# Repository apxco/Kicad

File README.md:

Ein Paar Projekte von mir zur Dokumentation und  vlt. ist es jemandem nützlich. 

Würde mich freuen jedenfalls.

Benutzung auf eigene Gefahr!

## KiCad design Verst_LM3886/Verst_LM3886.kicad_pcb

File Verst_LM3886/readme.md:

Verstärkermodul mit LM3886<br/>
<br/>
Für meine Bastelecke brauche ich einen Verstärker. Der sollte nicht hörbar rauschen oder brummen.  Was das vorhandene Modul auf Basis LM3886 leider tut. Zumindest bei niedrieger einstellung des Lautstärkepotis, warum auch immer. Ich bekomme es nicht abgestellt und da ich sowieso mehr Kanäle brauche, dieses Projekt.<br/>
<br/>
Ziele:<br/>
kein hörbares Rauschen oder Brummen.<br/>
Leistung, ich habe einen 16v Traffo und der Kühlkörper ist vorhanden, das muss genügen.
<br/>

04.01.2026  Erster Entwurf Schaltplan und Platine. 
07.02.2026  Erster Platinenentwurf fertiggestellt.
<br/>

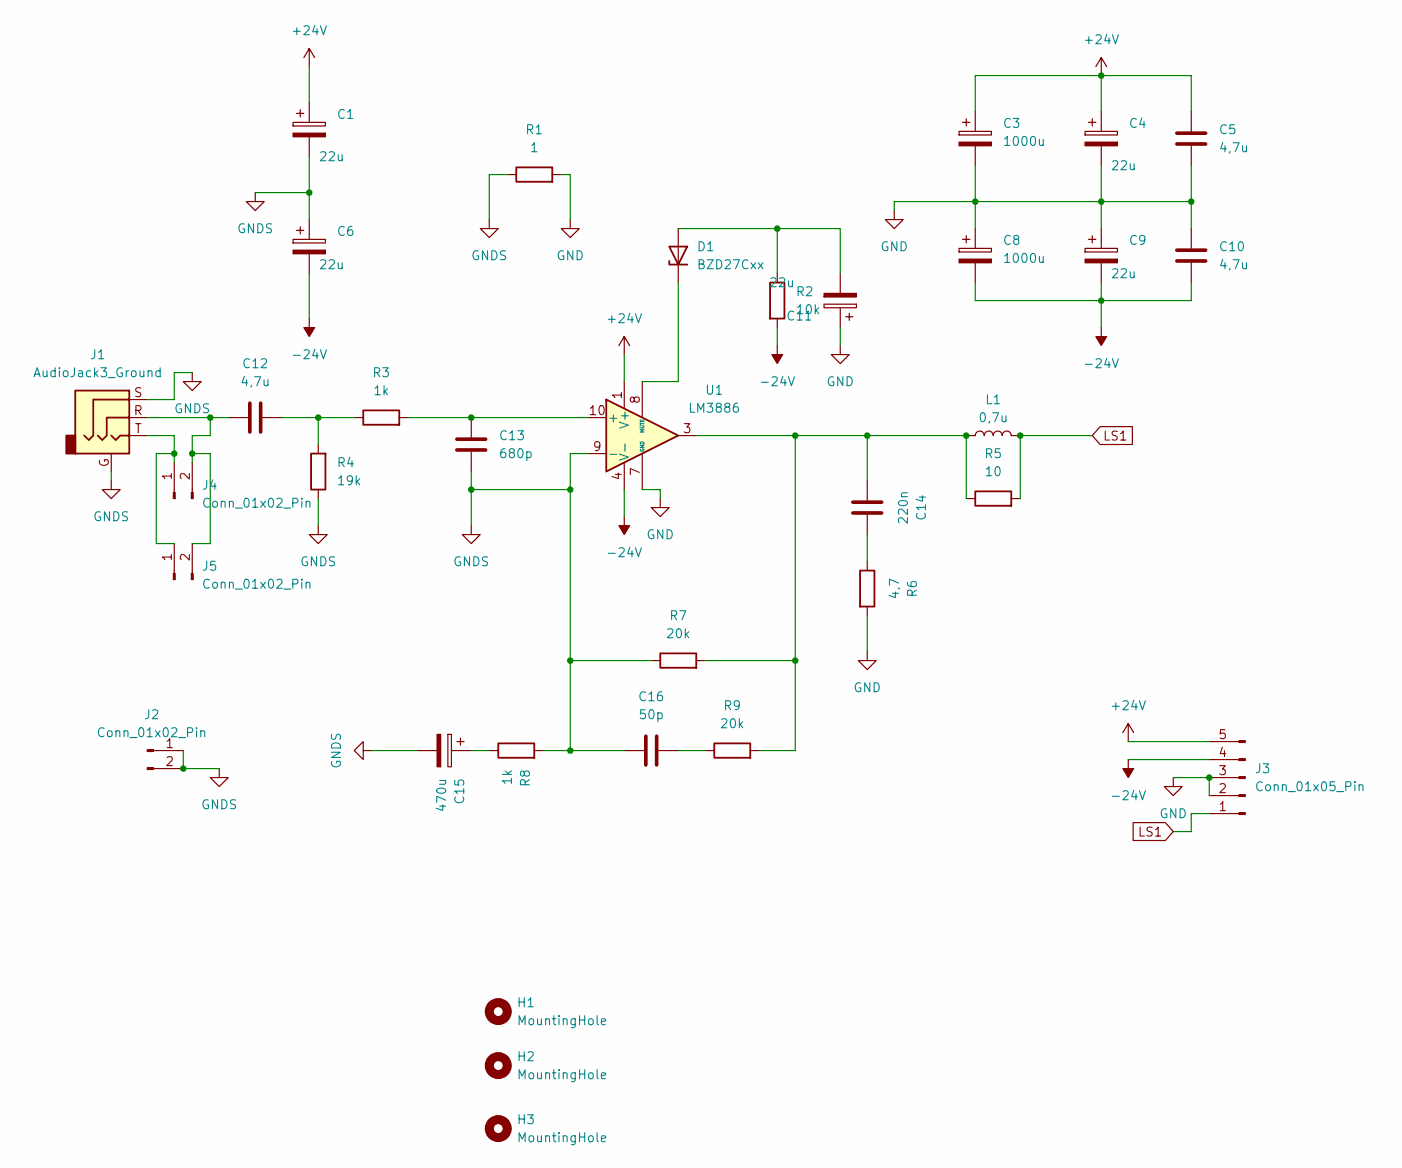
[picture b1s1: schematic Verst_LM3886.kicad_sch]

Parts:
C1, C4, C6, C9, C11: 22u; CP_Radial_D6.3mm_P2.50mm
C3, C8: 1000u; CP_Radial_D10.0mm_P5.00mm_P7.50mm
C5, C10: 4,7u; C_1210_3225Metric_Pad1.33x2.70mm_HandSolder
C12: 4,7u; C_Disc_D8.0mm_W5.0mm_P7.50mm
C13: 680p; C_Rect_L7.0mm_W3.5mm_P2.50mm_P5.00mm
C14: 220n; C_Rect_L7.0mm_W3.5mm_P2.50mm_P5.00mm
C15: 470u; C_Radial_D10.0mm_H20.0mm_P5.00mm
C16: 50p; C_0805_2012Metric_Pad1.18x1.45mm_HandSolder
D1: BZD27Cxx; D_SMF
H1, H2, H3: MountingHole; MountingHole_3.2mm_M3
J1: AudioJack3_Ground; Jack_3.5mm_PJ320E_Horizontal
J2: Conn_01x02_Pin; JST_NV_B02P-NV_1x02_P5.00mm_Vertical
J3: Conn_01x05_Pin; PhoenixContact_MSTBVA_2,5_5-G_1x05_P5.00mm_Vertical
J4, J5: Conn_01x02_Pin; PinHeader_1x02_P1.27mm_Vertical
L1: 0,7u; L_Radial_L9.1mm_W9.1mm_Px6.35mm_Py6.35mm_Pulse_LP-25
R1: 1; R_Axial_DIN0204_L3.6mm_D1.6mm_P2.54mm_Vertical
R2: 10k; R_0805_2012Metric_Pad1.20x1.40mm_HandSolder
R3, R8: 1k; R_0805_2012Metric_Pad1.20x1.40mm_HandSolder
R4: 19k; R_0805_2012Metric_Pad1.20x1.40mm_HandSolder
R5: 10; R_Axial_DIN0309_L9.0mm_D3.2mm_P12.70mm_Horizontal
R6: 4,7; R_Axial_DIN0309_L9.0mm_D3.2mm_P12.70mm_Horizontal
R7, R9: 20k; R_0805_2012Metric_Pad1.20x1.40mm_HandSolder
U1: LM3886; TO-220-11_P3.4x5.08mm_StaggerOdd_Lead4.58mm_Vertical

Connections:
+24V: C1.1, C3.1, C4.1, C5.1, J3.5, U1.1 (V+), U1.5 (V+)
-24V: C6.2, C8.2, C9.2, C10.2, J3.4, R2.2, U1.4 (V-)
GND: C3.2, C4.2, C5.2, C8.1, C9.1, C10.1, C11.1, J3.2, J3.3, R1.2, R6.2, U1.7 (GND)
GNDS: C1.2, C6.1, C13.1, C15.2, C16.1, J1.G, J1.S, J2.1, J2.2, R1.1, R4.1, R7.1, R8.2, U1.9 (-)
LS1: J3.1, L1.2, R5.2
unnamed: C12.1, R3.1, R4.2
unnamed: C14.1, L1.1, R5.1, R7.2, R9.2, U1.3
unnamed: C14.2, R6.1
unnamed: C15.1, R8.1
unnamed: C16.2, R9.1
unnamed: C11.2, D1.2 (A), R2.1
unnamed: D1.1 (K), U1.8 (MUTE)
unnamed: J1.T, J4.1, J5.1
unnamed: C12.2, J1.R, J4.2, J5.2
unnamed: C13.2, R3.2, U1.10 (+)

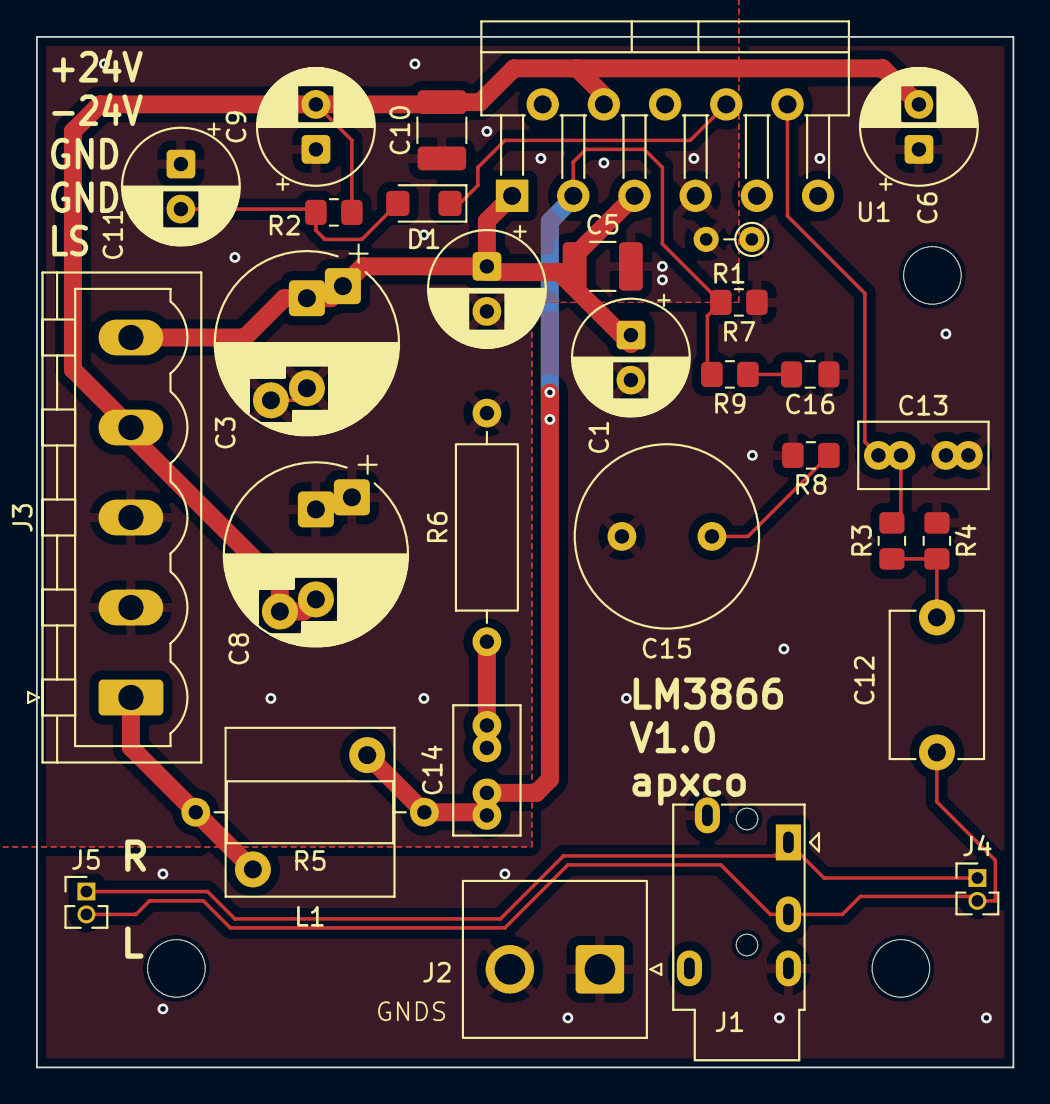
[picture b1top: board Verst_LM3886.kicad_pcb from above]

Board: 2 copper layers, 54.2 x 57.2 mm, 34 parts (0 on the bottom side), 15 nets.

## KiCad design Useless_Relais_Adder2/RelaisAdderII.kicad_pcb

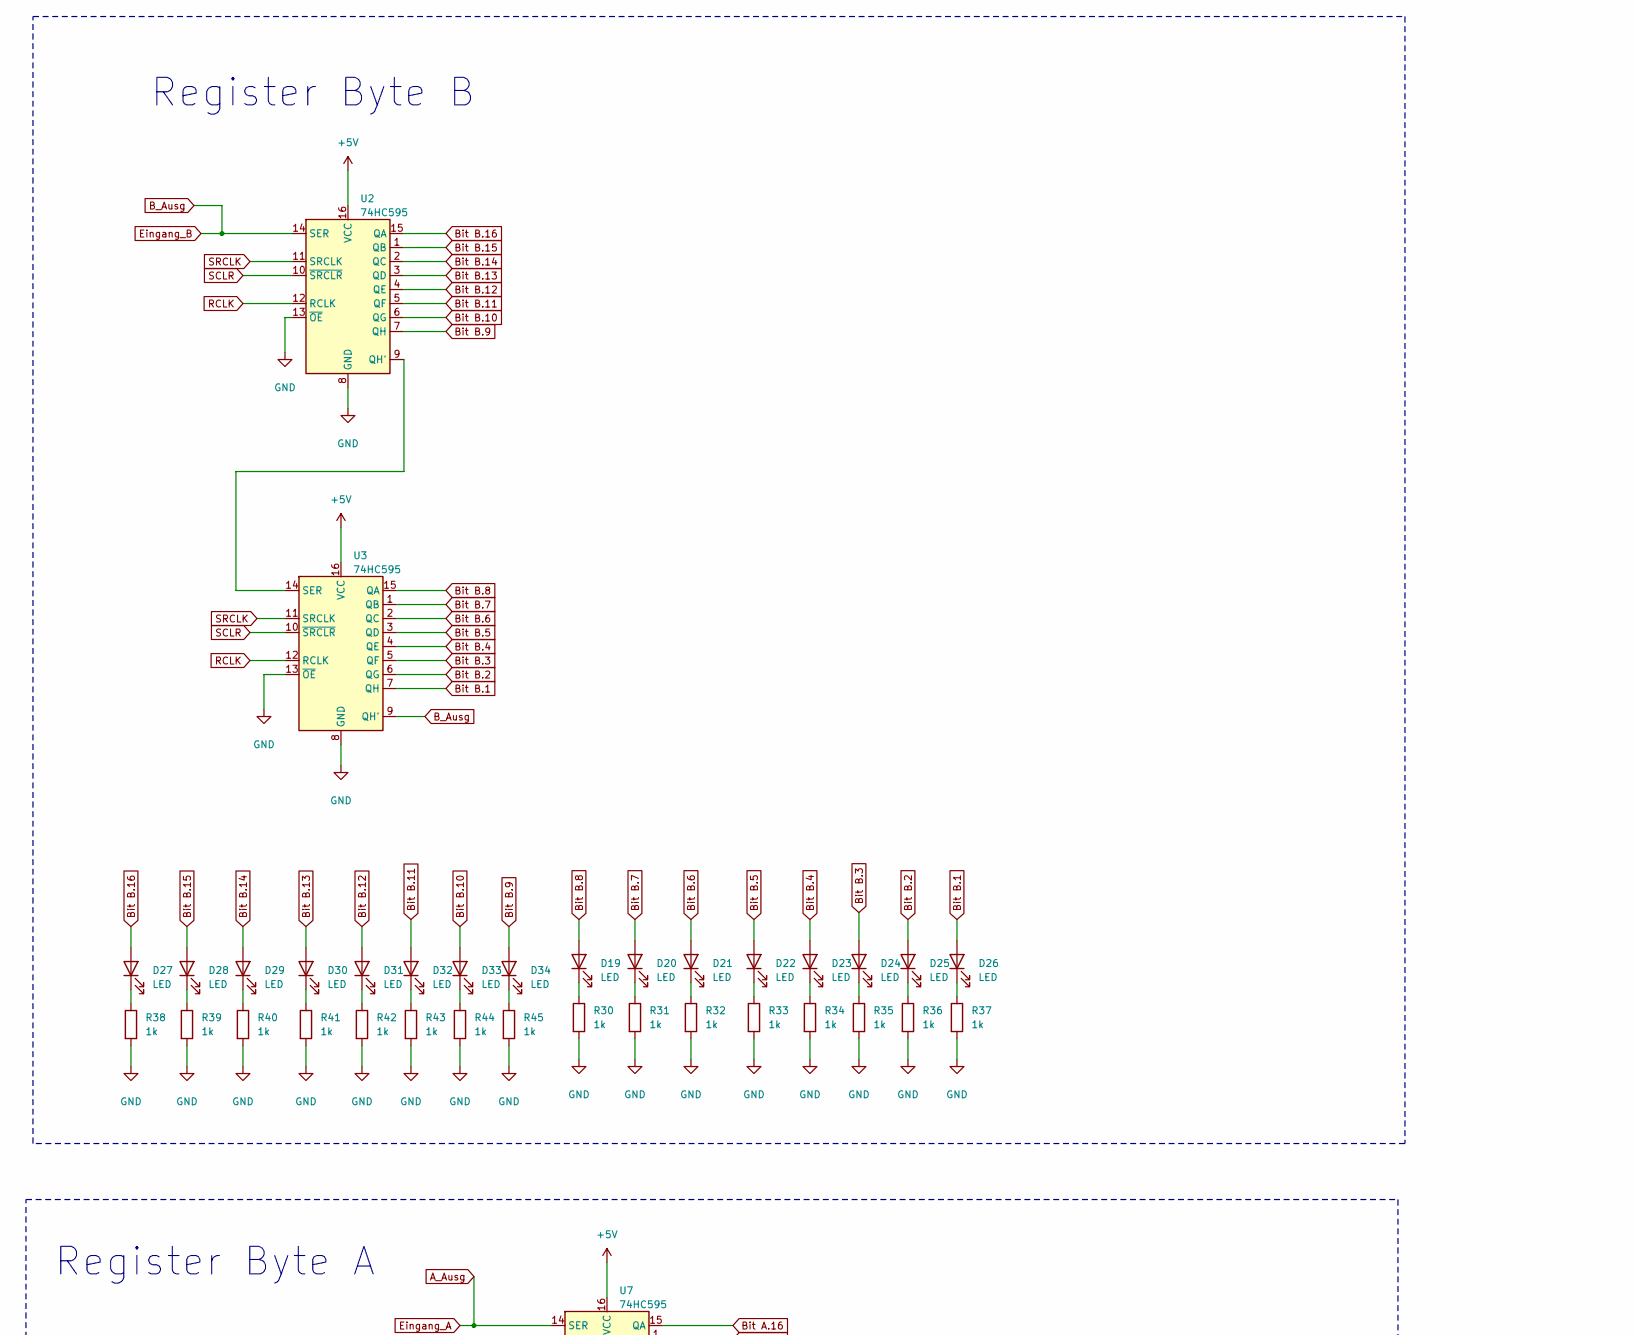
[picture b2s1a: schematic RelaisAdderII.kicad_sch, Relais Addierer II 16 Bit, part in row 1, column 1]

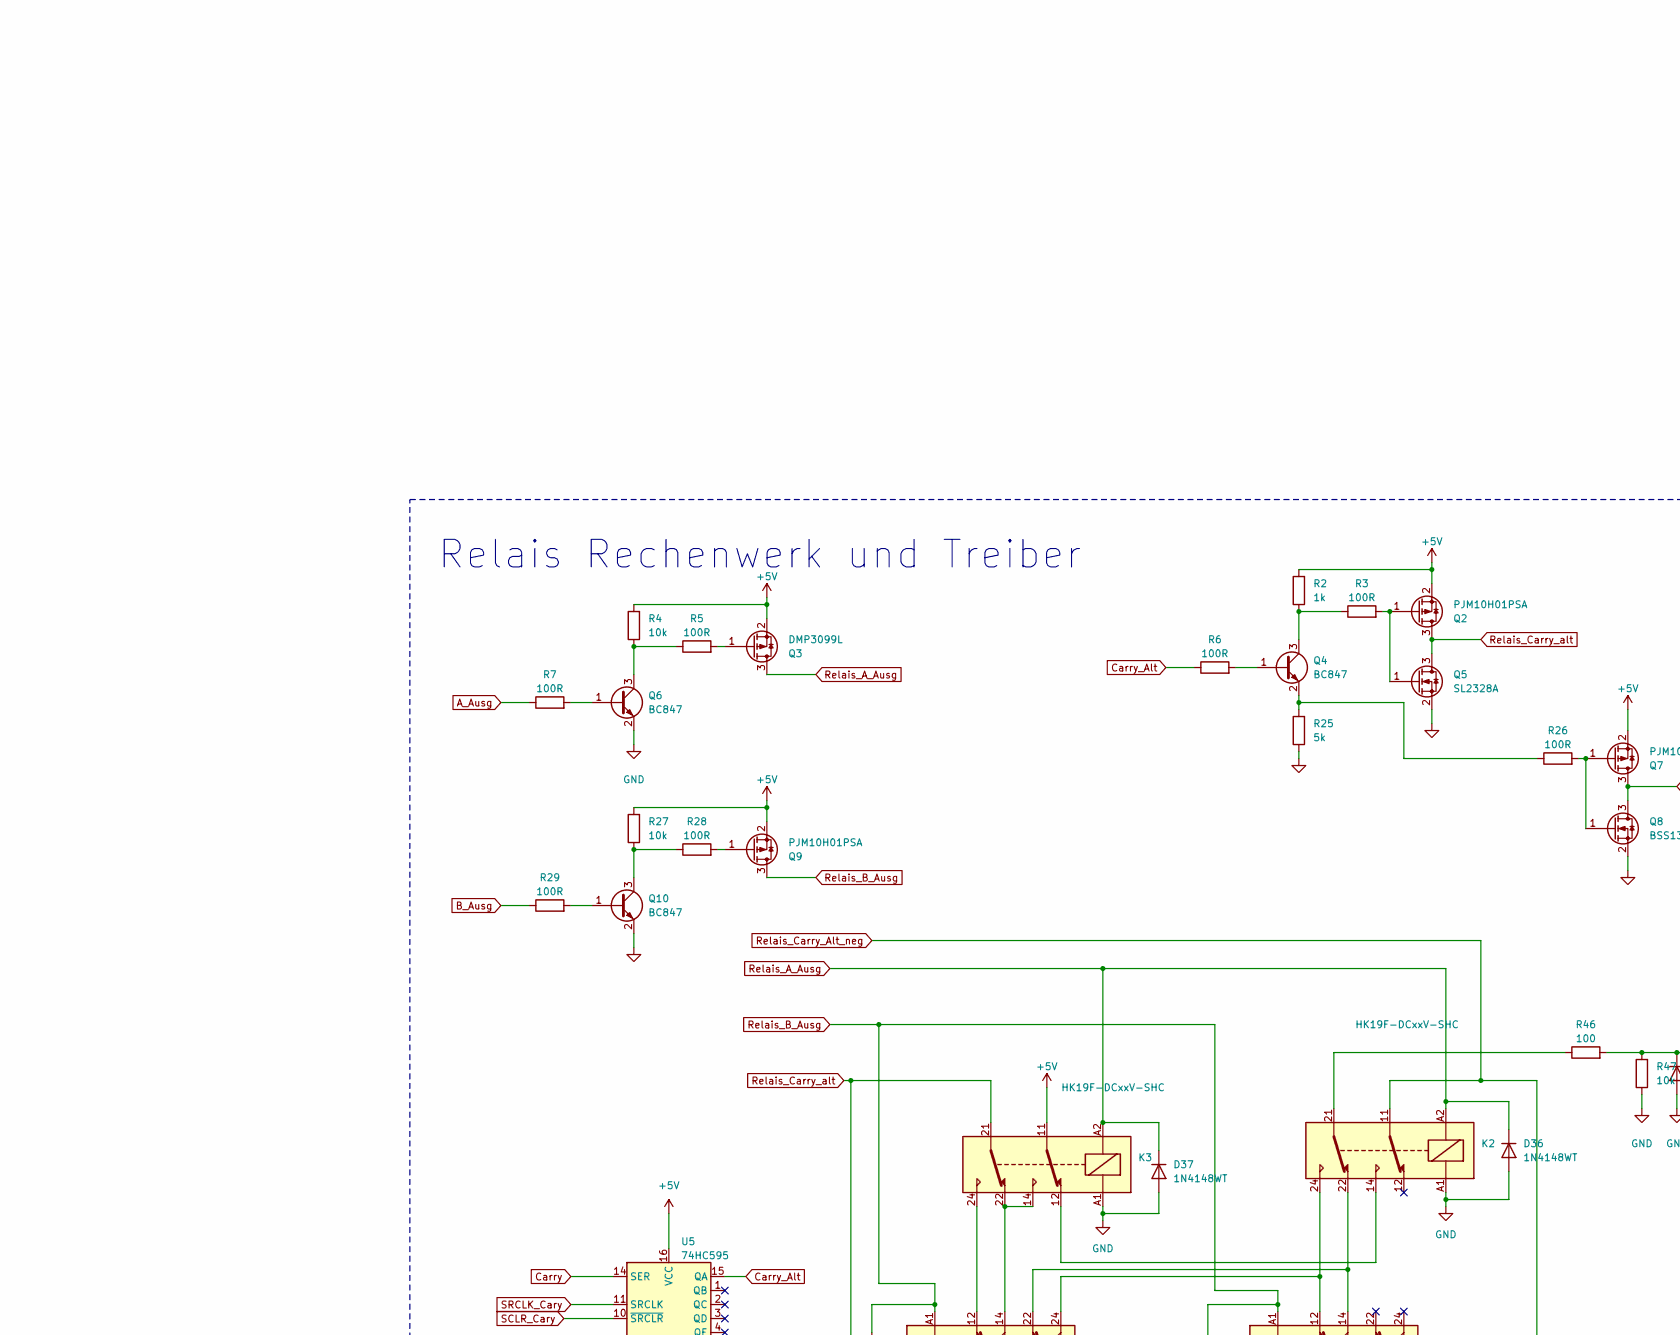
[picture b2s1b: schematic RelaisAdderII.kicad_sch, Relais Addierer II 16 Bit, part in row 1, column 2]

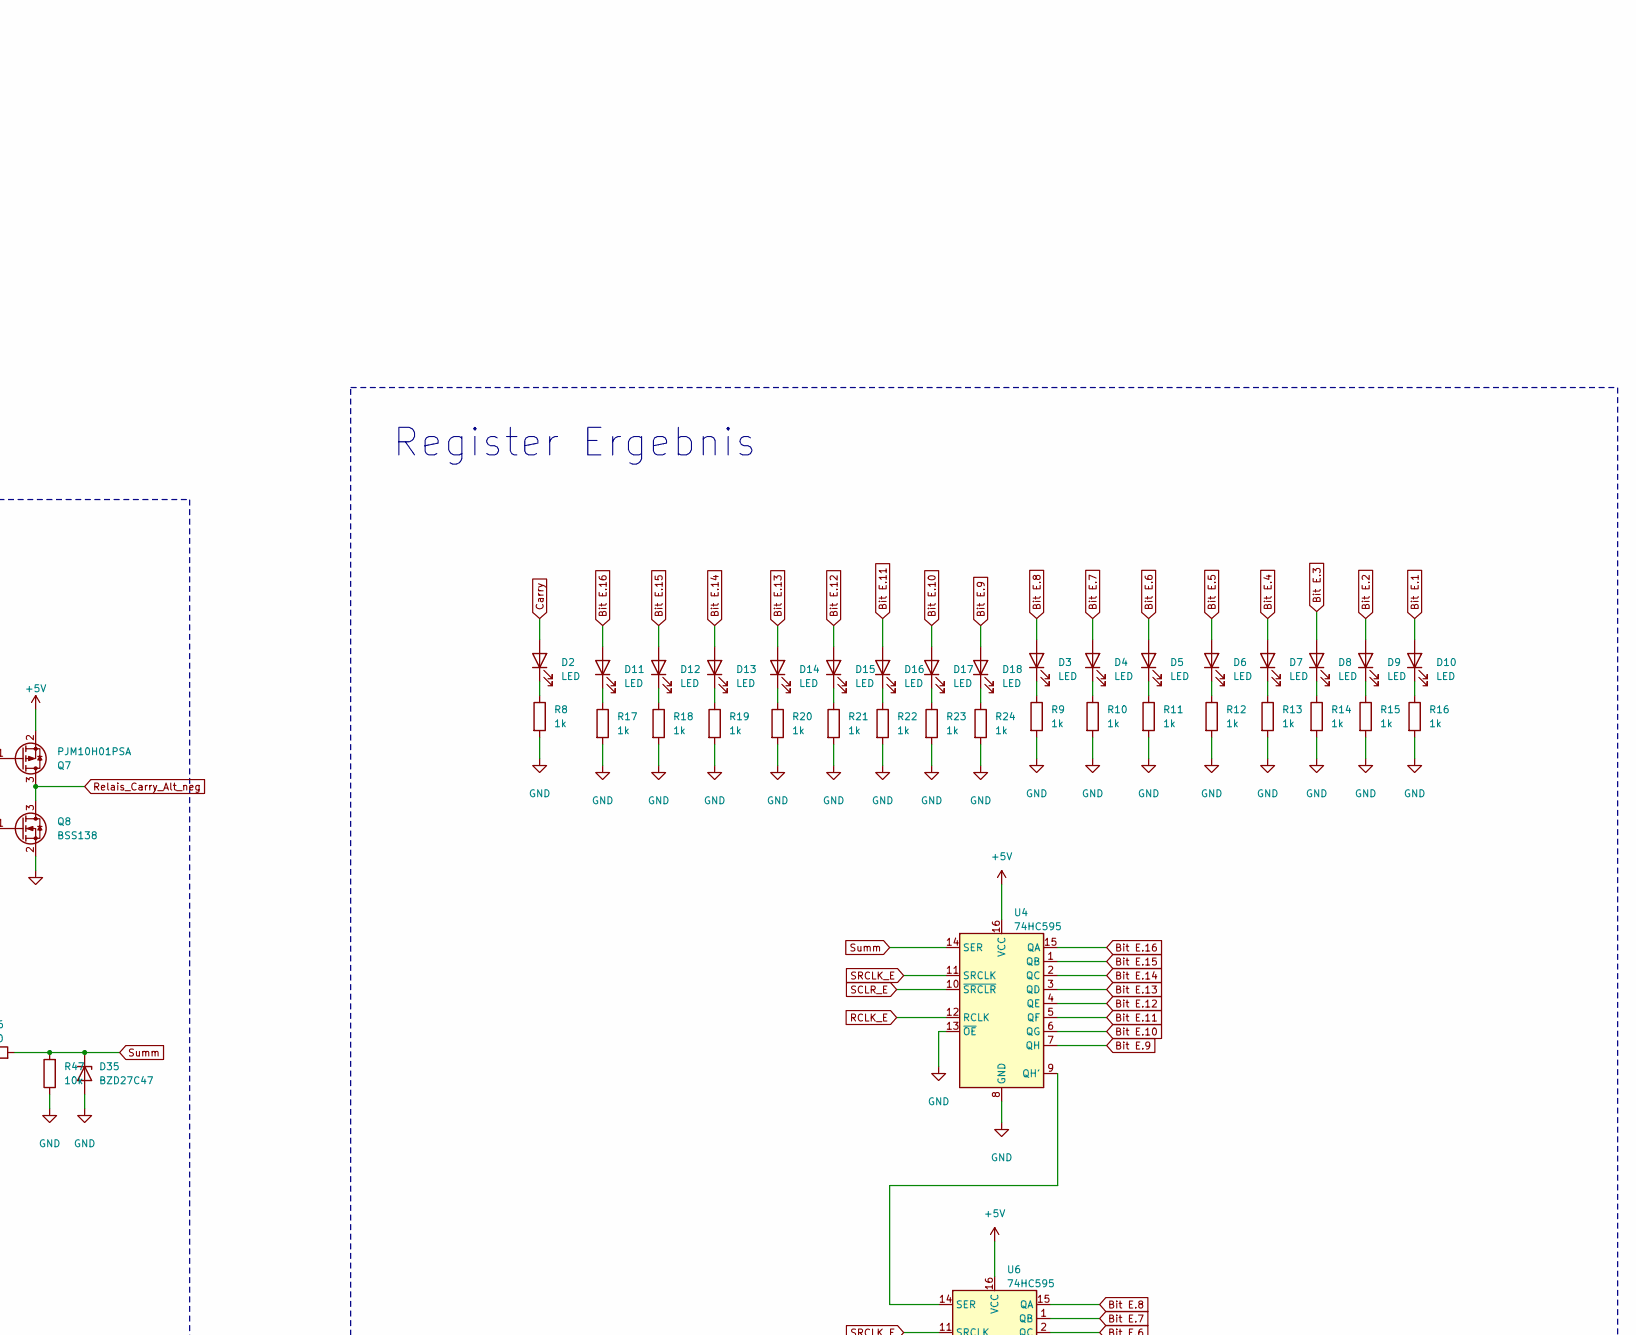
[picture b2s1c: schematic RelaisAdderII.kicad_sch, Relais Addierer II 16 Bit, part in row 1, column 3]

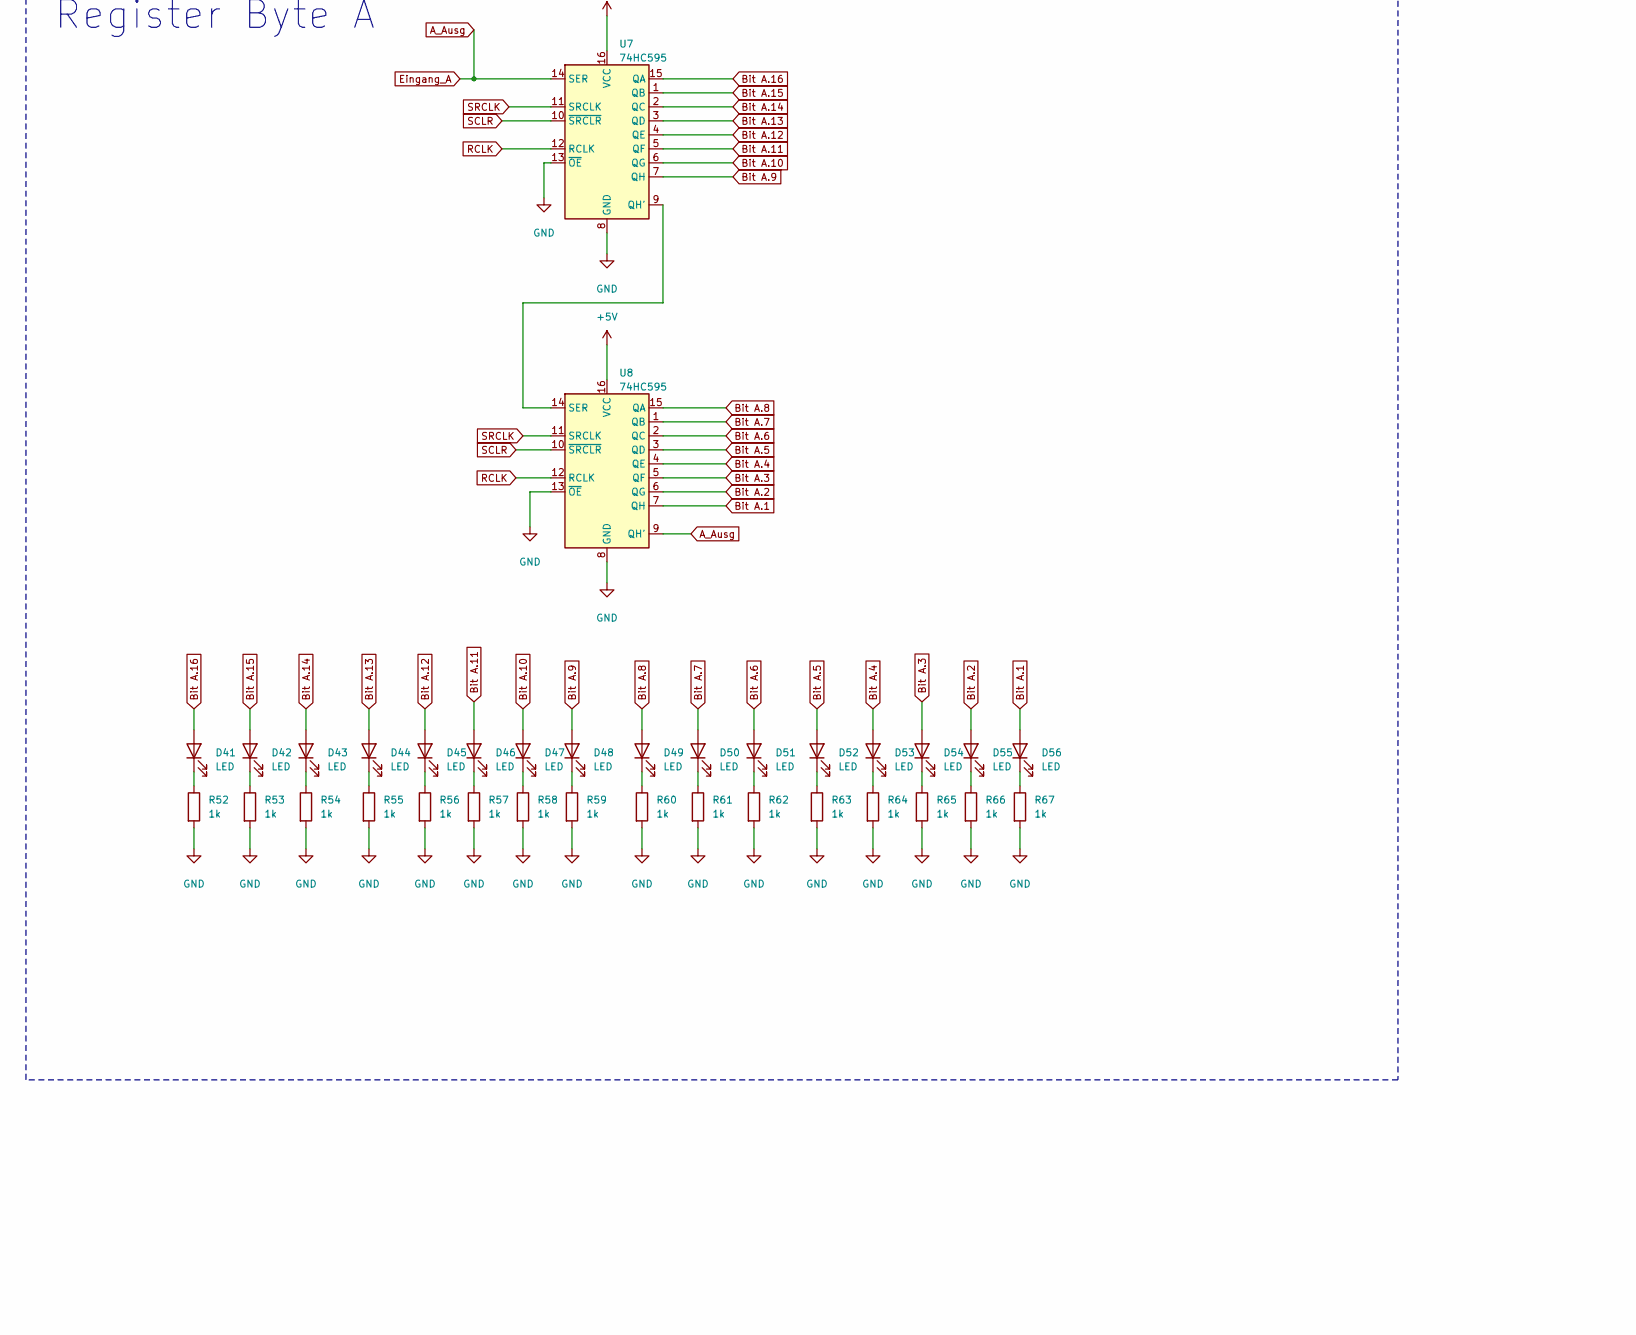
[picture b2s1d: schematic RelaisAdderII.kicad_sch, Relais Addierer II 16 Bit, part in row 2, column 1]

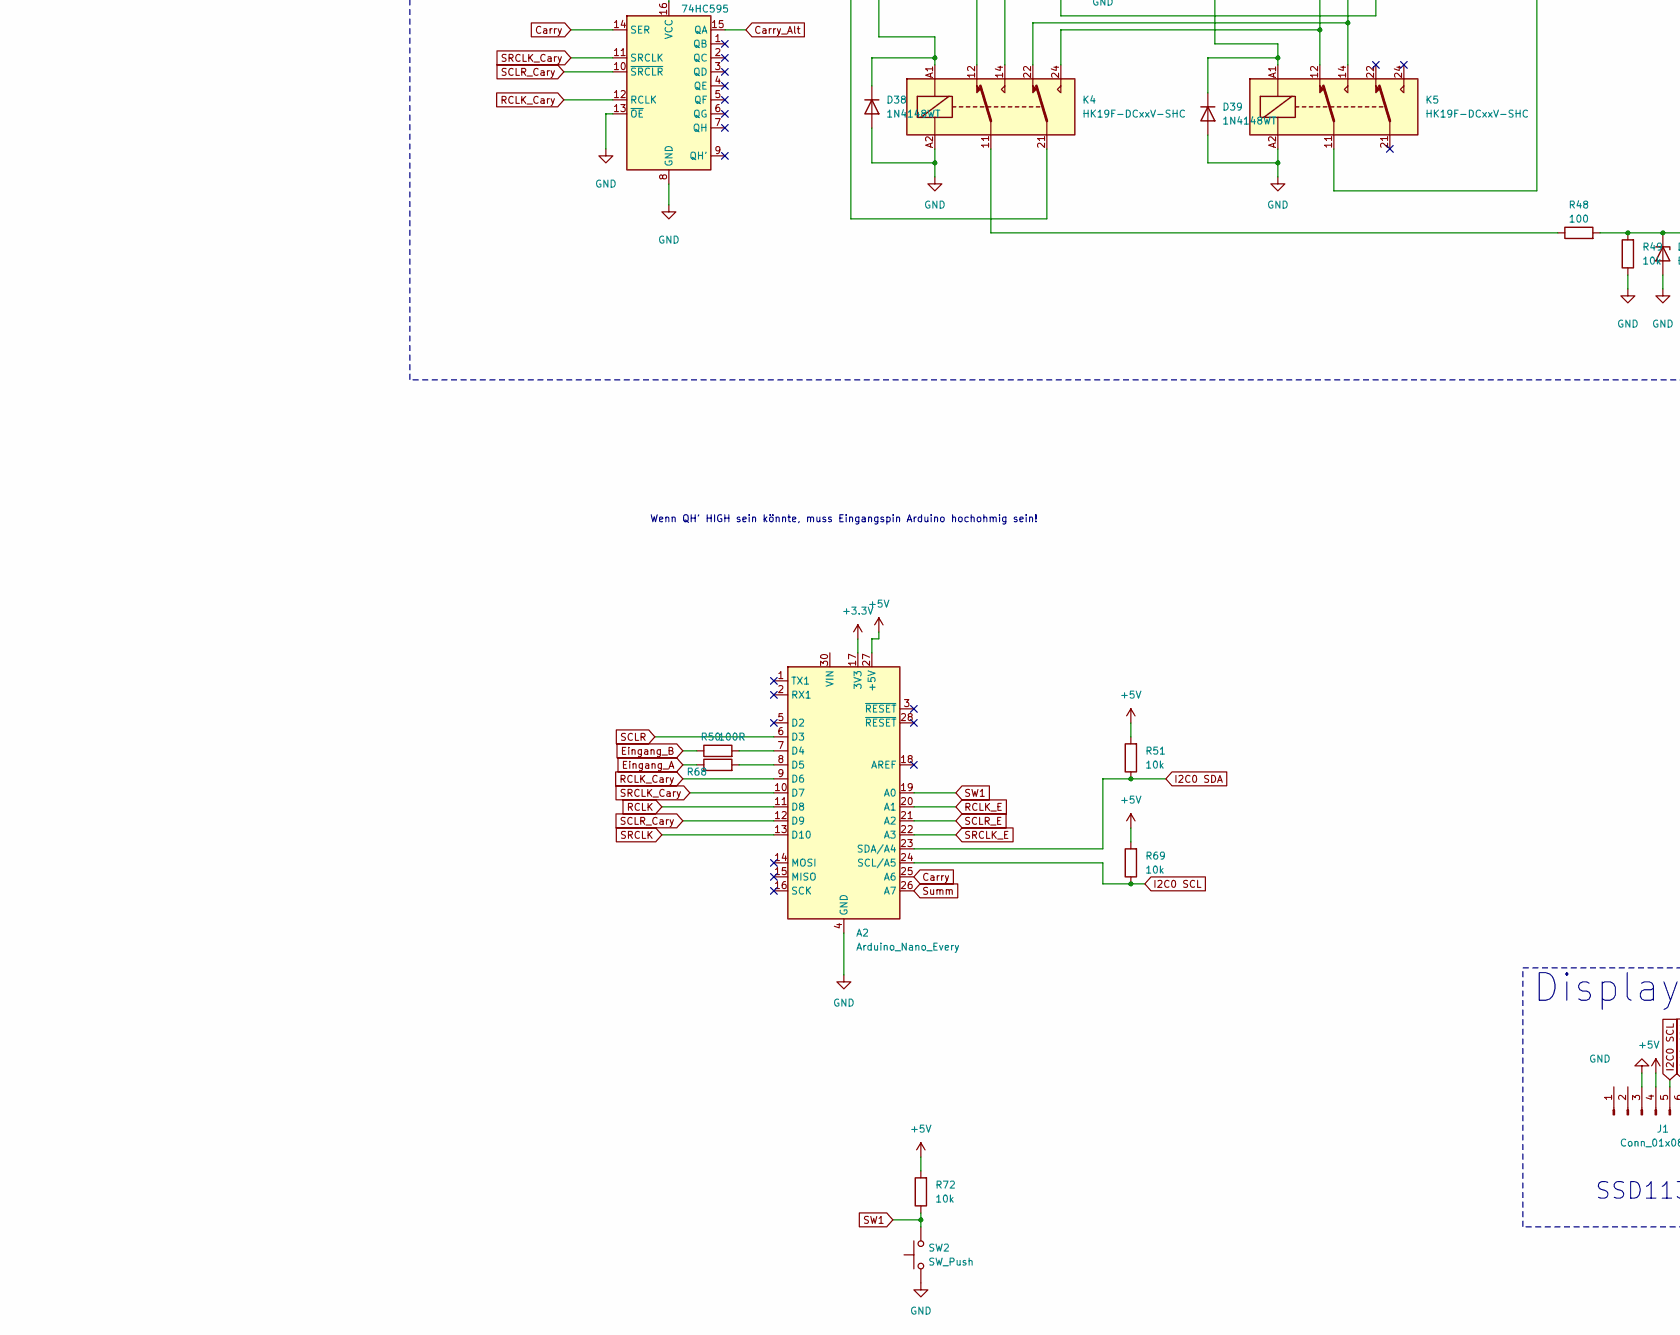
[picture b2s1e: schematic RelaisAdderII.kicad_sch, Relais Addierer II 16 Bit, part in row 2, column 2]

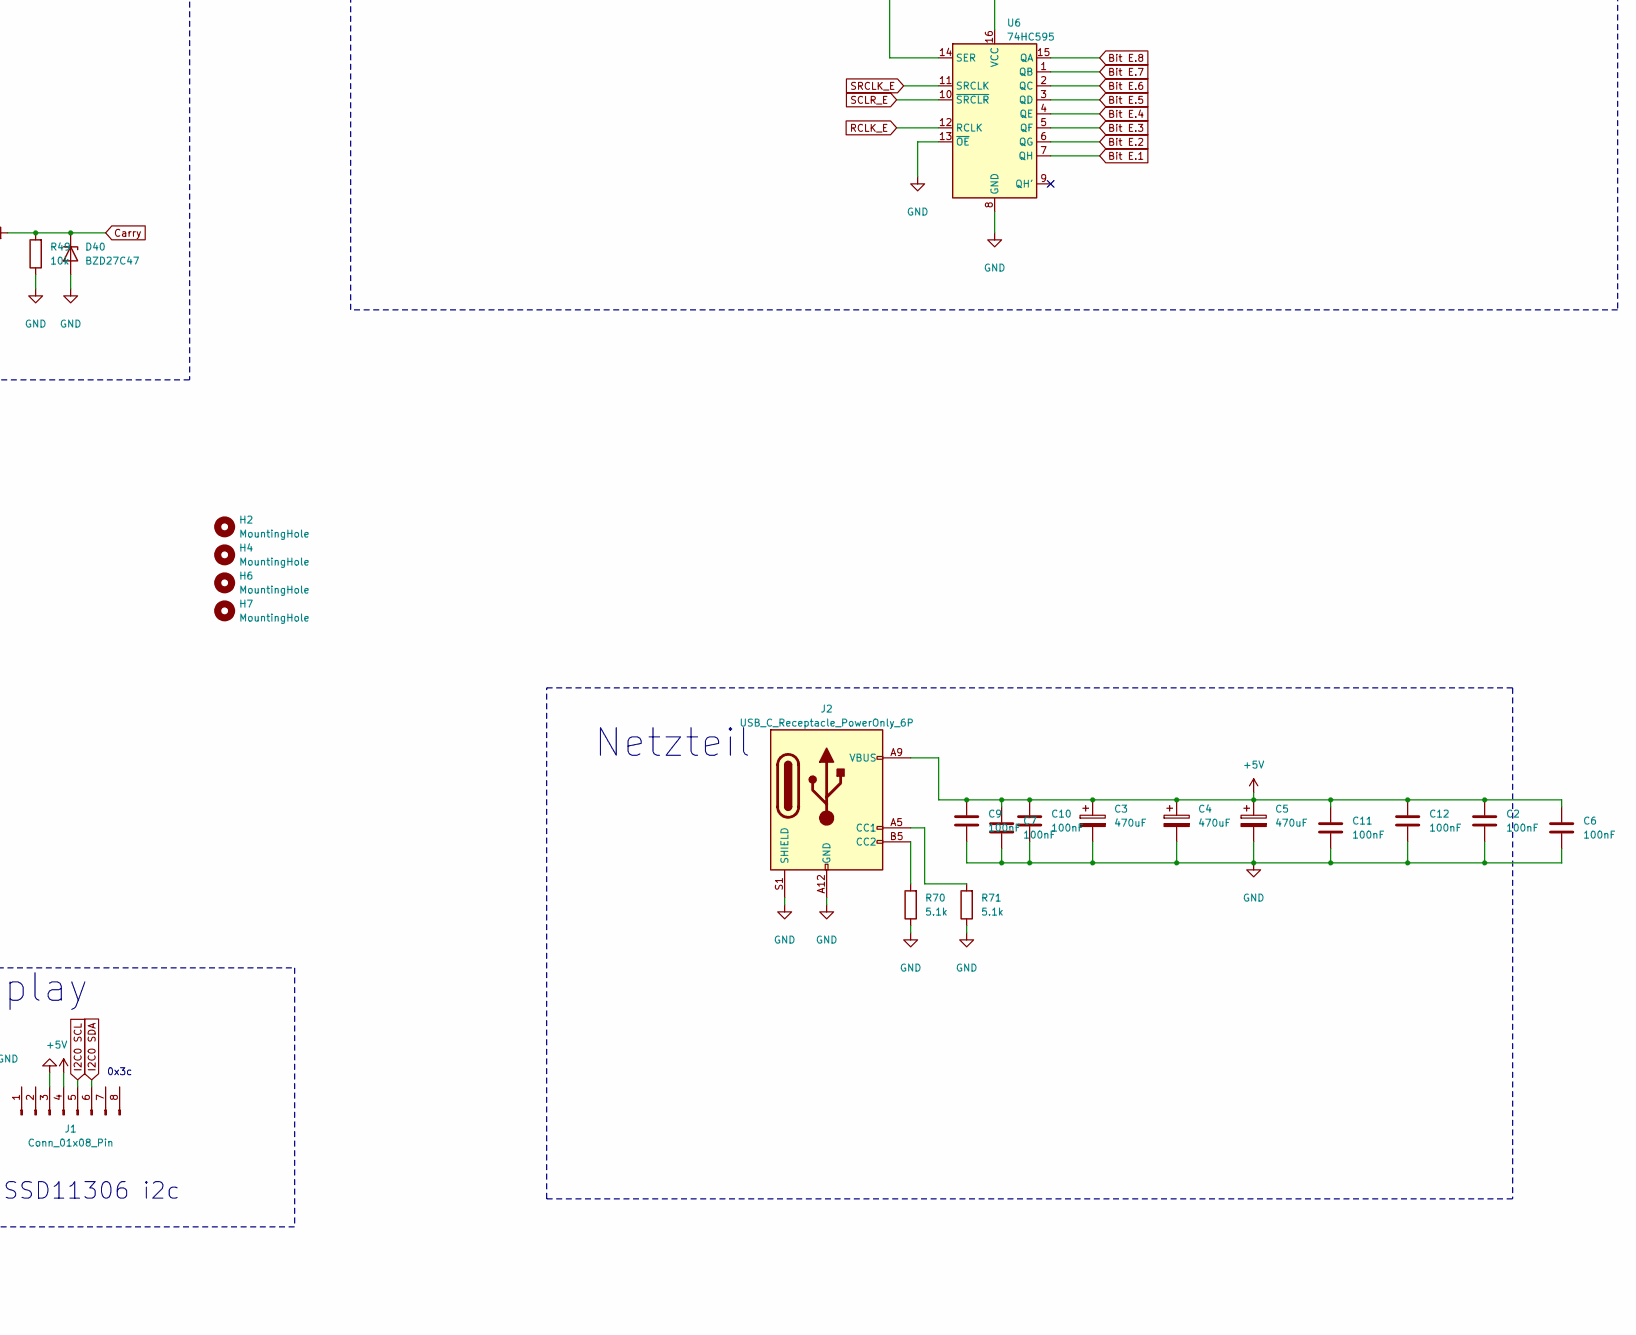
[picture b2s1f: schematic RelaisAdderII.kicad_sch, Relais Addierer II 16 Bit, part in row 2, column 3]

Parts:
A2: Arduino_Nano_Every; Arduino_Nano
C2, C6, C7, C9, C10, C11, C12: 100nF; C_0805_2012Metric_Pad1.18x1.45mm_HandSolder
C3, C4, C5: 470uF; CP_Elec_10x12.5
D2, D3, D4, D5, D6, D7, D8, D9, D10, D11, D12, D13, D14, D15, D16, D17, D18, D19, D20, D21, D22, D23, D24, D25, D26, D27, D28, D29, D30, D31, D32, D33, D34, D41, D42, D43, D44, D45, D46, D47, D48, D49, D50, D51, D52, D53, D54, D55, D56: LED; LED_0805_2012Metric_Pad1.15x1.40mm_HandSolder
D35, D40: BZD27C47; D_MiniMELF
D36, D37, D38, D39: 1N4148WT; D_SMF
H2, H4, H6, H7: MountingHole; MountingHole_4.3mm_M4_DIN965
J1: Conn_01x08_Pin; PinHeader_1x08_P2.54mm_Vertical
J2: USB_C_Receptacle_PowerOnly_6P; USB_C_Receptacle_GCT_USB4125-xx-x-0190_6P_TopMnt_Horizontal
K2, K3, K4, K5: HK19F-DCxxV-SHC; Relay_DPDT_Finder_30.22
Q2, Q7, Q9: PJM10H01PSA; SOT-23
Q3: DMP3099L; SOT-23
Q4, Q6, Q10: BC847; SOT-23
Q5: SL2328A; SOT-23
Q8: BSS138; SOT-23
R2, R8, R9, R10, R11, R12, R13, R14, R15, R16, R17, R18, R19, R20, R21, R22, R23, R24, R30, R31, R32, R33, R34, R35, R36, R37, R38, R39, R40, R41, R42, R43, R44, R45, R52, R53, R54, R55, R56, R57, R58, R59, R60, R61, R62, R63, R64, R65, R66, R67: 1k; R_0805_2012Metric_Pad1.20x1.40mm_HandSolder
R3, R5, R6, R7, R26, R28, R29, R50, R68: 100R; R_0805_2012Metric_Pad1.20x1.40mm_HandSolder
R4, R27, R47, R49, R51, R69, R72: 10k; R_0805_2012Metric_Pad1.20x1.40mm_HandSolder
R25: 5k; R_0805_2012Metric_Pad1.20x1.40mm_HandSolder
R46, R48: 100; R_0805_2012Metric_Pad1.20x1.40mm_HandSolder
R70, R71: 5.1k; R_0805_2012Metric_Pad1.20x1.40mm_HandSolder
SW2: SW_Push; SW_PUSH_6mm_H5mm
U2, U3, U4, U5, U6, U7, U8: 74HC595; SOIC-16_3.9x9.9mm_P1.27mm

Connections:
+3.3V: A2.17 (3V3)
+5V: A2.27 (+5V), C2.1, C3.1, C4.1, C5.1, C6.1, C7.1, C9.1, C10.1, C11.1, C12.1, J1.4, J2.A9 (VBUS), J2.B9 (VBUS), K3.11, Q2.2 (S), Q3.2 (S), Q7.2 (S), Q9.2 (S), R2.2, R4.2, R27.2, R51.2, R69.2, R72.2, U2.16 (VCC), U3.16 (VCC), U4.16 (VCC), U5.16 (VCC), U6.16 (VCC), U7.16 (VCC), U8.16 (VCC)
A_Ausg: R7.1, R68.1, U7.14 (SER), U8.9 (QH')
B_Ausg: R29.1, R50.1, U2.14 (SER), U3.9 (QH')
Bit A.1: D56.2 (A), U8.7 (QH)
Bit A.2: D55.2 (A), U8.6 (QG)
Bit A.3: D54.2 (A), U8.5 (QF)
Bit A.4: D53.2 (A), U8.4 (QE)
Bit A.5: D52.2 (A), U8.3 (QD)
Bit A.6: D51.2 (A), U8.2 (QC)
Bit A.7: D50.2 (A), U8.1 (QB)
Bit A.8: D49.2 (A), U8.15 (QA)
Bit A.9: D48.2 (A), U7.7 (QH)
Bit A.10: D47.2 (A), U7.6 (QG)
Bit A.11: D46.2 (A), U7.5 (QF)
Bit A.12: D45.2 (A), U7.4 (QE)
Bit A.13: D44.2 (A), U7.3 (QD)
Bit A.14: D43.2 (A), U7.2 (QC)
Bit A.15: D42.2 (A), U7.1 (QB)
Bit A.16: D41.2 (A), U7.15 (QA)
Bit B.1: D26.2 (A), U3.7 (QH)
Bit B.2: D25.2 (A), U3.6 (QG)
Bit B.3: D24.2 (A), U3.5 (QF)
Bit B.4: D23.2 (A), U3.4 (QE)
Bit B.5: D22.2 (A), U3.3 (QD)
Bit B.6: D21.2 (A), U3.2 (QC)
Bit B.7: D20.2 (A), U3.1 (QB)
Bit B.8: D19.2 (A), U3.15 (QA)
Bit B.9: D34.2 (A), U2.7 (QH)
Bit B.10: D33.2 (A), U2.6 (QG)
Bit B.11: D32.2 (A), U2.5 (QF)
Bit B.12: D31.2 (A), U2.4 (QE)
Bit B.13: D30.2 (A), U2.3 (QD)
Bit B.14: D29.2 (A), U2.2 (QC)
Bit B.15: D28.2 (A), U2.1 (QB)
Bit B.16: D27.2 (A), U2.15 (QA)
Bit E.1: D10.2 (A), U6.7 (QH)
Bit E.2: D9.2 (A), U6.6 (QG)
Bit E.3: D8.2 (A), U6.5 (QF)
Bit E.4: D7.2 (A), U6.4 (QE)
Bit E.5: D6.2 (A), U6.3 (QD)
Bit E.6: D5.2 (A), U6.2 (QC)
Bit E.7: D4.2 (A), U6.1 (QB)
Bit E.8: D3.2 (A), U6.15 (QA)
Bit E.9: D18.2 (A), U4.7 (QH)
Bit E.10: D17.2 (A), U4.6 (QG)
Bit E.11: D16.2 (A), U4.5 (QF)
Bit E.12: D15.2 (A), U4.4 (QE)
Bit E.13: D14.2 (A), U4.3 (QD)
Bit E.14: D13.2 (A), U4.2 (QC)
Bit E.15: D12.2 (A), U4.1 (QB)
Bit E.16: D11.2 (A), U4.15 (QA)
Carry: A2.25 (A6), D2.2 (A), D40.1 (K), R48.2, R49.2, U5.14 (SER)
Carry_Alt: R6.1, U5.15 (QA)
GND: A2.4 (GND), A2.29 (GND), C2.2, C3.2, C4.2, C5.2, C6.2, C7.2, C9.2, C10.2, C11.2, C12.2, D35.2 (A), D36.2 (A), D37.2 (A), D38.2 (A), D39.2 (A), D40.2 (A), J1.3, J2.A12 (GND), J2.B12 (GND), J2.S1 (SHIELD), K2.A1, K3.A1, K4.A2, K5.A2, Q5.2 (S), Q6.2 (E), Q8.2 (S), Q10.2 (E), R8.2, R9.2, R10.2, R11.2, R12.2, R13.2, R14.2, R15.2, R16.2, R17.2, R18.2, R19.2, R20.2, R21.2, R22.2, R23.2, R24.2, R25.1, R30.2, R31.2, R32.2, R33.2, R34.2, R35.2, R36.2, R37.2, R38.2, R39.2, R40.2, R41.2, R42.2, R43.2, R44.2, R45.2, R47.1, R49.1, R52.2, R53.2, R54.2, R55.2, R56.2, R57.2, R58.2, R59.2, R60.2, R61.2, R62.2, R63.2, R64.2, R65.2, R66.2, R67.2, R70.1, R71.1, SW2.1, U2.8 (GND), U2.13 (~OE), U3.8 (GND), U3.13 (~OE), U4.8 (GND), U4.13 (~OE), U5.8 (GND), U5.13 (~OE), U6.8 (GND), U6.13 (~OE), U7.8 (GND), U7.13 (~OE), U8.8 (GND), U8.13 (~OE)
I2C0 SCL: A2.24 (SCL/A5), J1.5, R69.1
I2C0 SDA: A2.23 (SDA/A4), J1.6, R51.1
unnamed: A2.7 (D4), R50.2
unnamed: A2.8 (D5), R68.2
unnamed: D2.1 (K), R8.1
unnamed: D3.1 (K), R9.1
unnamed: D4.1 (K), R10.1
unnamed: D5.1 (K), R11.1
unnamed: D6.1 (K), R12.1
unnamed: D7.1 (K), R13.1
unnamed: D8.1 (K), R14.1
unnamed: D9.1 (K), R15.1
unnamed: D10.1 (K), R16.1
unnamed: D11.1 (K), R17.1
unnamed: D12.1 (K), R18.1
unnamed: D13.1 (K), R19.1
unnamed: D14.1 (K), R20.1
unnamed: D15.1 (K), R21.1
unnamed: D16.1 (K), R22.1
unnamed: D17.1 (K), R23.1
unnamed: D18.1 (K), R24.1
unnamed: D19.1 (K), R30.1
unnamed: D20.1 (K), R31.1
unnamed: D21.1 (K), R32.1
unnamed: D22.1 (K), R33.1
unnamed: D23.1 (K), R34.1
unnamed: D24.1 (K), R35.1
unnamed: D25.1 (K), R36.1
unnamed: D26.1 (K), R37.1
unnamed: D27.1 (K), R38.1
unnamed: D28.1 (K), R39.1
unnamed: D29.1 (K), R40.1
unnamed: D30.1 (K), R41.1
unnamed: D31.1 (K), R42.1
unnamed: D32.1 (K), R43.1
unnamed: D33.1 (K), R44.1
unnamed: D34.1 (K), R45.1
unnamed: D41.1 (K), R52.1
unnamed: D42.1 (K), R53.1
unnamed: D43.1 (K), R54.1
unnamed: D44.1 (K), R55.1
unnamed: D45.1 (K), R56.1
unnamed: D46.1 (K), R57.1
unnamed: D47.1 (K), R58.1
unnamed: D48.1 (K), R59.1
unnamed: D49.1 (K), R60.1
unnamed: D50.1 (K), R61.1
unnamed: D51.1 (K), R62.1
unnamed: D52.1 (K), R63.1
unnamed: D53.1 (K), R64.1
unnamed: D54.1 (K), R65.1
unnamed: D55.1 (K), R66.1
unnamed: D56.1 (K), R67.1
unnamed: J2.A5 (CC1), R71.2
unnamed: J2.B5 (CC2), R70.2
unnamed: K2.14, K3.12
unnamed: K2.21, R46.1
unnamed: K2.22, K4.22, K5.14
unnamed: K2.24, K4.24, K5.12
unnamed: K3.14, K3.22, K4.14
unnamed: K3.24, K4.12
unnamed: K4.11, R48.1
unnamed: Q2.1 (G), Q5.1 (G), R3.2
unnamed: Q3.1 (G), R5.2
unnamed: Q4.1 (B), R6.2
unnamed: Q4.3 (C), R2.1, R3.1
unnamed: Q4.2 (E), R25.2, R26.1
unnamed: Q6.1 (B), R7.2
unnamed: Q6.3 (C), R4.1, R5.1
unnamed: Q7.1 (G), Q8.1 (G), R26.2
unnamed: Q9.1 (G), R28.2
unnamed: Q10.1 (B), R29.2
unnamed: Q10.3 (C), R27.1, R28.1
unnamed: U2.9 (QH'), U3.14 (SER)
unnamed: U4.9 (QH'), U6.14 (SER)
unnamed: U7.9 (QH'), U8.14 (SER)
RCLK: A2.11 (D8), U2.12 (RCLK), U3.12 (RCLK), U7.12 (RCLK), U8.12 (RCLK)
RCLK_Cary: A2.9 (D6), U5.12 (RCLK)
RCLK_E: A2.20 (A1), U4.12 (RCLK), U6.12 (RCLK)
Relais_A_Ausg: D36.1 (K), D37.1 (K), K2.A2, K3.A2, Q3.3 (D)
Relais_B_Ausg: D38.1 (K), D39.1 (K), K4.A1, K5.A1, Q9.3 (D)
Relais_Carry_Alt_neg: K2.11, K5.11, Q7.3 (D), Q8.3 (D)
Relais_Carry_alt: K3.21, K4.21, Q2.3 (D), Q5.3 (D)
SCLR: A2.6 (D3), U2.10 (~SRCLR), U3.10 (~SRCLR), U7.10 (~SRCLR), U8.10 (~SRCLR)
SCLR_Cary: A2.12 (D9), U5.10 (~SRCLR)
SCLR_E: A2.21 (A2), U4.10 (~SRCLR), U6.10 (~SRCLR)
SRCLK: A2.13 (D10), U2.11 (SRCLK), U3.11 (SRCLK), U7.11 (SRCLK), U8.11 (SRCLK)
SRCLK_Cary: A2.10 (D7), U5.11 (SRCLK)
SRCLK_E: A2.22 (A3), U4.11 (SRCLK), U6.11 (SRCLK)
SW1: A2.19 (A0), R72.1, SW2.2
Summ: A2.26 (A7), D35.1 (K), R46.2, R47.2, U4.14 (SER)

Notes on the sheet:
Register Ergebnis
Netzteil
Register Byte A
Register Byte B
Display
Wenn QH' HIGH sein könnte, muss Eingangspin Arduino hochohmig sein!
SSD11306 i2c
Relais Rechenwerk und Treiber
0x3c
